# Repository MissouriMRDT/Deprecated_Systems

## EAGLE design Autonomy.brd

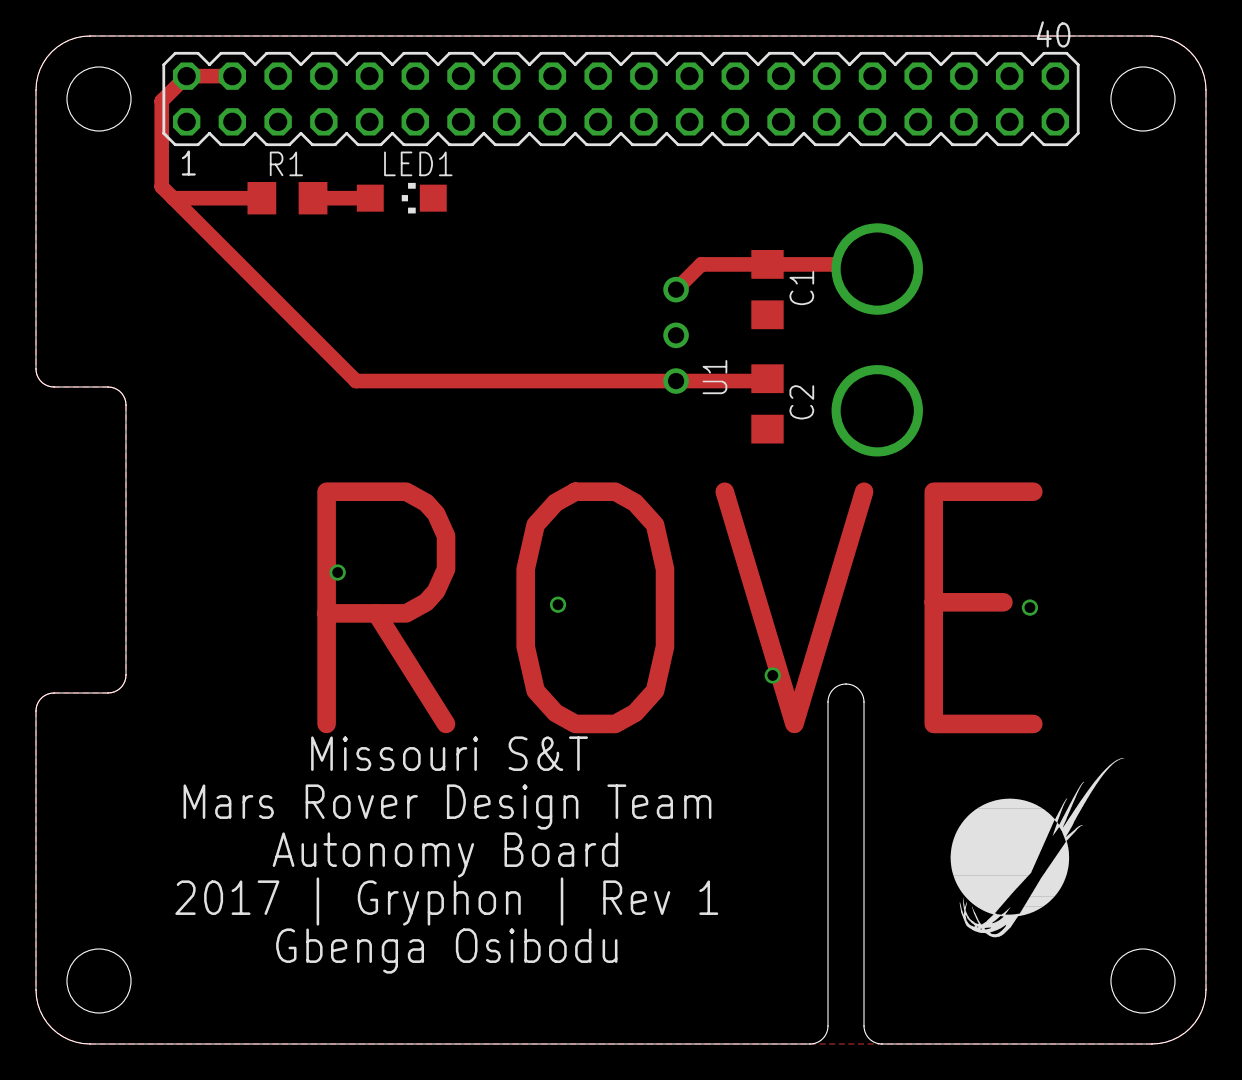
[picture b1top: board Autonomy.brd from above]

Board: 2 copper layers, 65.0 x 56.0 mm, 12 parts (0 on the bottom side), 4 nets.

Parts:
C1, C2: 10uF; C1206
J1: APP_2POS_CONFIG12V_HORIZ; APP45_12V_HORIZ_CONFIG
K1: MA20-2
LED1: CHIPLED_1206
R1: 330; R1206
U1: OKI-78SR-5/1.5-W36HC; OKI-78SR_HORIZ
U$1, U$2, U$3, U$4: #6_SCREW
U$5: MRDT_LOGO

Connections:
+5V: C2.1, K1.2, K1.4, R1.1, U1.3
+12V: C1.1, J1.12V, U1.1
GND: C1.2, C2.2, J1.GND, K1.6, K1.9, K1.14, K1.20, K1.25, K1.30, K1.34, K1.39, LED1.C, U1.2
unnamed: LED1.A, R1.2

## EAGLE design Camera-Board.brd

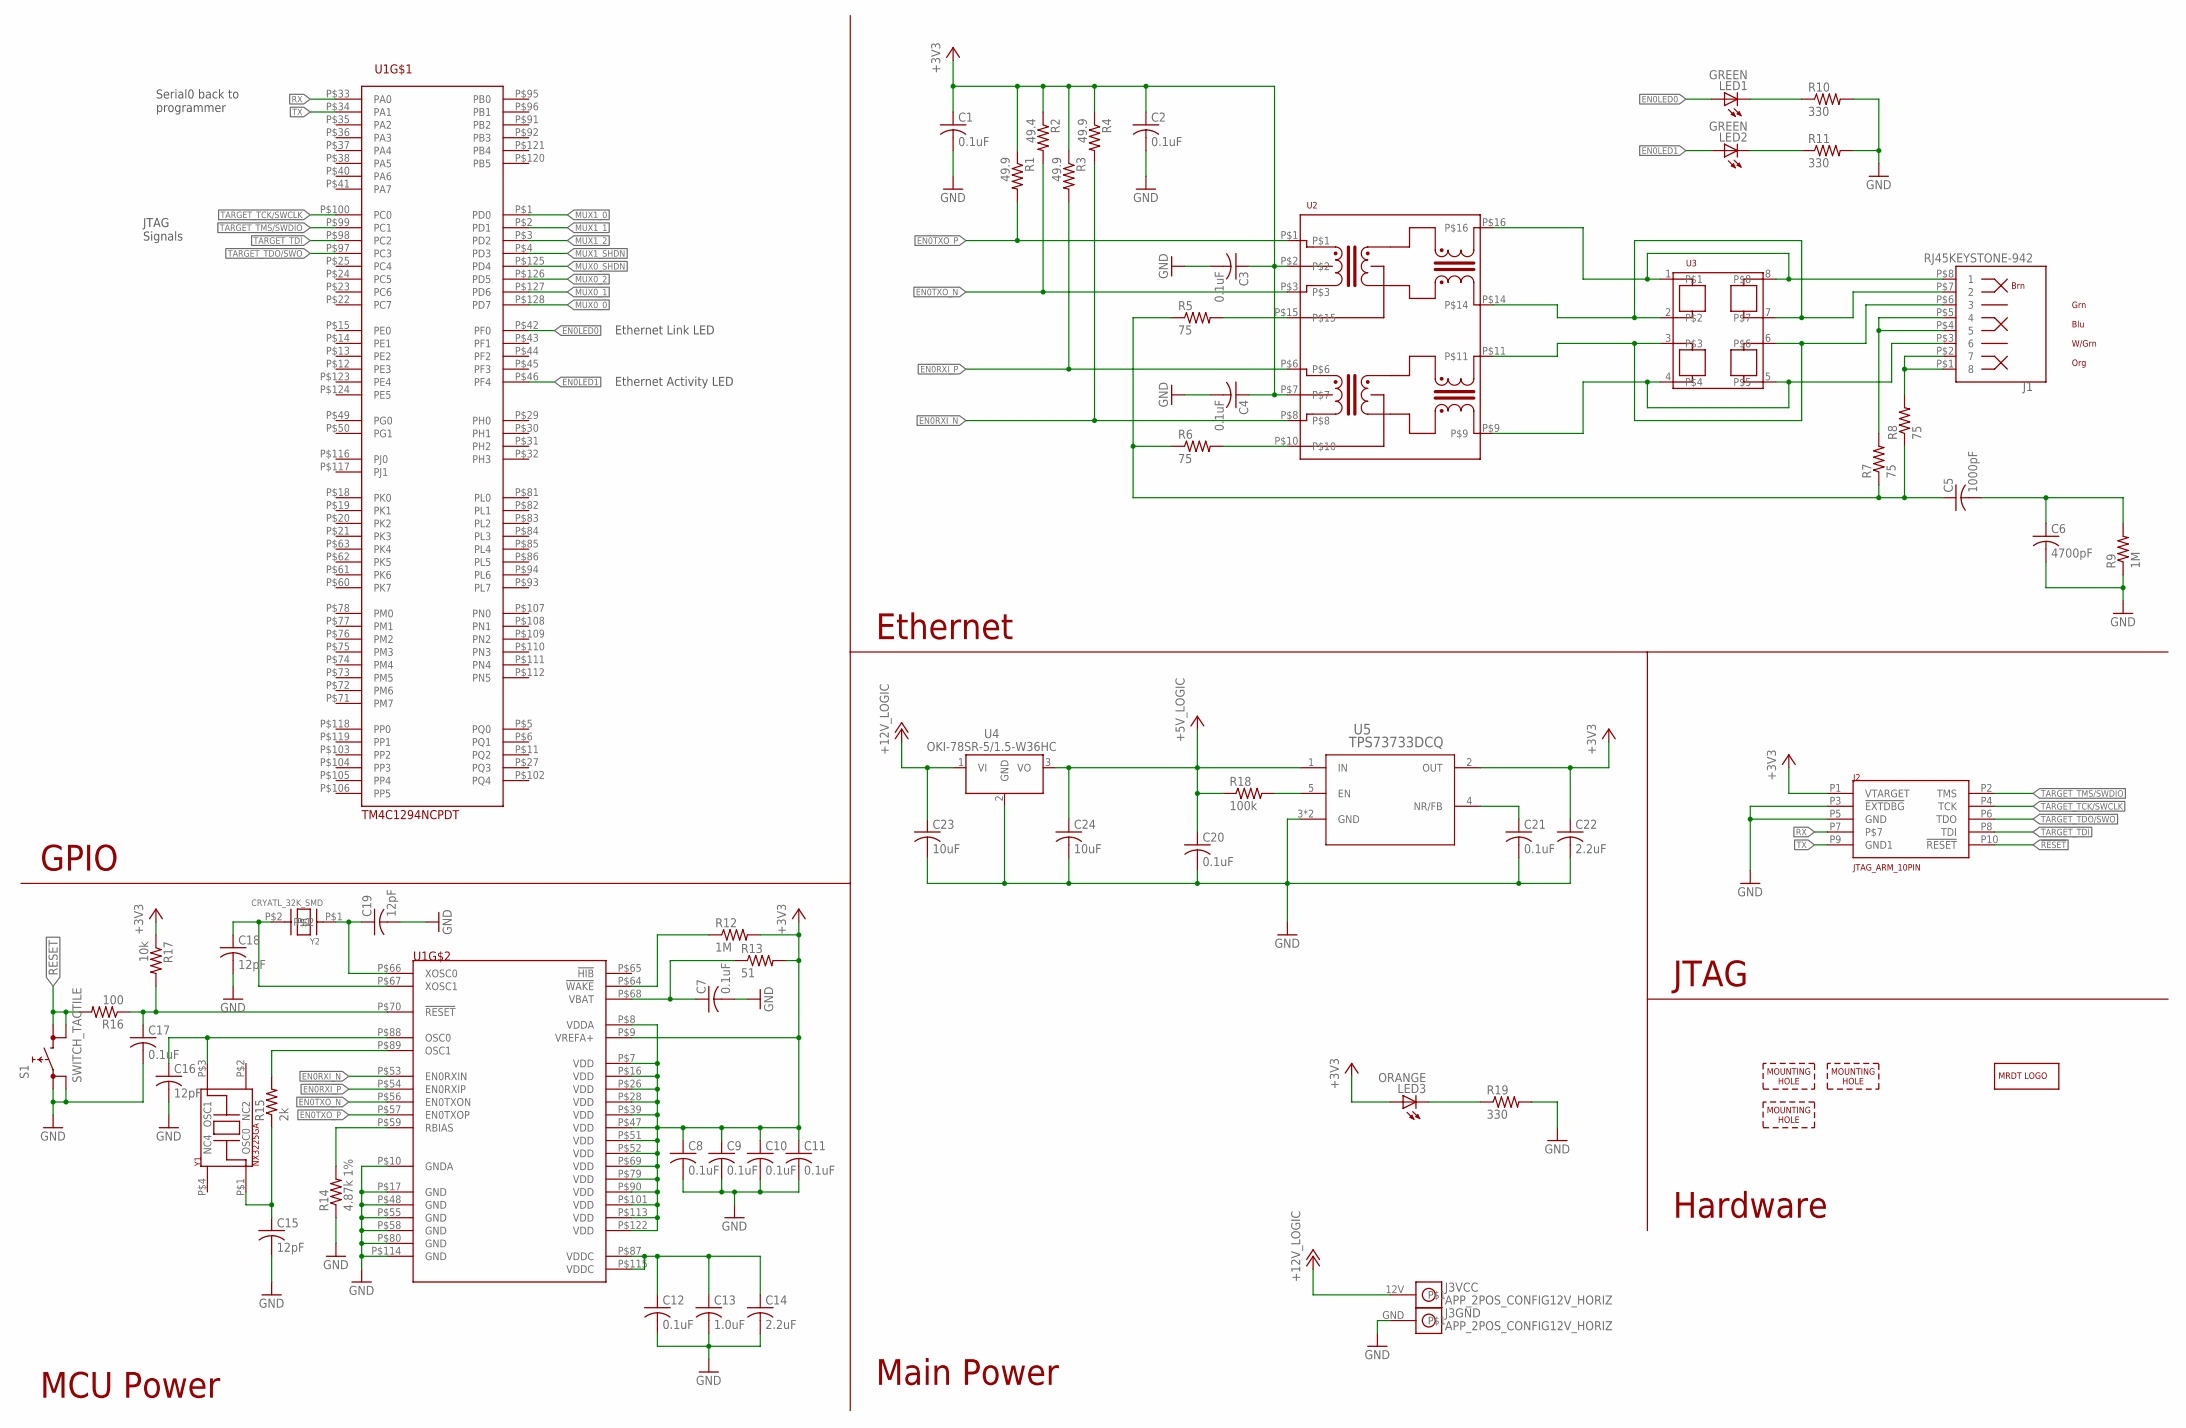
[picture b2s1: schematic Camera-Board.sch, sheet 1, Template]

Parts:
C1, C2, C3, C4, C7, C8, C9, C10, C11, C12, C17, C20, C21: 0.1uF; C0603
C5: 1000pF; C0603
C6: 4700pF; C1206
C13: 1.0uF; C0603
C14, C22: 2.2uF; C0603
C15, C16, C18, C19: 12pF; C0603
C23, C24: 10uF; C1206
J1: RJ45KEYSTONE-942; KEYSTONE-942
J2: JTAG_ARM_10PIN; CON_2X5_50MIL
J3: APP_2POS_CONFIG12V_HORIZ; APP45_12V_HORIZ_CONFIG
LED1, LED2: GREEN; CHIP-LED0603
LED3: ORANGE; CHIP-LED0603
R1, R3, R4: 49.9; R0603
R2: 49.4; R0603
R5, R6, R7, R8: 75; R0603
R9: 1M; R1206
R10, R11, R19: 330; R0603
R12: 1M; R0603
R13: 51; R0603
R14: 4.87k 1%; R0603
R15: 2k; R0603
R16: 100; R0603
R17: 10k; R0603
R18: 100k; R0603
S1: SWITCH_TACTILE; SWITCH_6MM_6MM_TE_CON_SMD
U1: TM4C1294NCPDT; TQFP-128
U2: HX1198FNL
U3: SLVU2.8-4; SOIC8
U4: OKI-78SR-5/1.5-W36HC; OKI-78SR_HORIZ
U5: TPS73733DCQ; SOT-223-6
U$1: MRDT_LOGO
U$2, U$3, U$4: MOUNTING_HOLE#6; #6_SCREW
Y1: NX3225GA; NDK3.2X2.5
Y2: CRYATL_32K_SMD; CRYSTAL_32K_SMD

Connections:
!RESET: J2.P10 (!RESET), R16.2, S1.P$3 (1), S1.P$4 (1)
+3V3: C1.1, C2.1, C3.1, C4.1, C8.1, C9.1, C10.1, C11.1, C22.1, J2.P1 (VTARGET), LED3.A, R1.1, R2.1, R3.1, R4.1, R12.2, R13.2, R17.1, U1.P$7 (VDD), U1.P$8 (VDDA), U1.P$9 (VREFA+), U1.P$16 (VDD), U1.P$26 (VDD), U1.P$28 (VDD), U1.P$39 (VDD), U1.P$47 (VDD), U1.P$51 (VDD), U1.P$52 (VDD), U1.P$69 (VDD), U1.P$79 (VDD), U1.P$90 (VDD), U1.P$101 (VDD), U1.P$113 (VDD), U1.P$122 (VDD), U2.P$2, U2.P$7, U5.2 (OUT)
+5V_LOGIC: C20.1, C24.1, R18.1, U4.3 (VO), U5.1 (IN); also elsewhere on the board
+12V_LOGIC: C23.1, J3.12V, U4.1 (VI)
EN0LED0: LED1.A, U1.P$42 (PF0)
EN0LED1: LED2.A, U1.P$46 (PF4)
EN0RXI_N: R4.2, U1.P$53 (EN0RXIN), U2.P$8
EN0RXI_P: R3.2, U1.P$54 (EN0RXIP), U2.P$6
EN0TXO_N: R2.2, U1.P$56 (EN0TXON), U2.P$3
EN0TXO_P: R1.2, U1.P$57 (EN0TXOP), U2.P$1
GND: C1.2, C2.2, C3.2, C4.2, C6.2, C7.2, C8.2, C9.2, C10.2, C11.2, C12.2, C13.2, C14.2, C15.2, C16.2, C17.2, C18.2, C19.2, C20.2, C21.2, C22.2, C23.2, C24.2, J2.P3 (!EXTDBG), J2.P5 (GND), J3.GND, R9.1, R10.2, R11.2, R14.1, R19.2, S1.P$1 (0), S1.P$2 (0), U1.P$10 (GNDA), U1.P$17 (GND), U1.P$48 (GND), U1.P$55 (GND), U1.P$58 (GND), U1.P$80 (GND), U1.P$114 (GND), U4.2 (GND), U5.3 (GND), U5.6 (GND); also elsewhere on the board
MUX0_0: U1.P$1 (PD0); also elsewhere on the board
MUX0_1: U1.P$2 (PD1); also elsewhere on the board
MUX0_2: U1.P$3 (PD2); also elsewhere on the board
MUX0_SHDN: U1.P$4 (PD3); also elsewhere on the board
MUX1_0: U1.P$128 (PD7); also elsewhere on the board
MUX1_1: U1.P$127 (PD6); also elsewhere on the board
MUX1_2: U1.P$126 (PD5); also elsewhere on the board
MUX1_SHDN: U1.P$125 (PD4); also elsewhere on the board
N_$1: R5.2, U2.P$15
N_$3: R6.2, U2.P$10
N_$4: J1.P$7 (2), U2.P$14, U3.2, U3.7
N_$5: J1.P$6 (3), U2.P$11, U3.3, U3.6
N_$6: J1.P$8 (1), U2.P$16, U3.1, U3.8
N_$7: J1.P$3 (6), U2.P$9, U3.4, U3.5
N_$8: LED2.C, R11.1
N_$9: LED1.C, R10.1
N_$10: C7.1, R13.1, U1.P$68 (VBAT)
N_$11: J1.P$4 (5), J1.P$5 (4), R7.2
N_$12: R12.1, U1.P$64 (!WAKE)
N_$13: J1.P$1 (8), J1.P$2 (7), R8.2
N_$14: C5.1, R5.1, R6.1, R7.1, R8.1
N_$15: C5.2, C6.1, R9.2
N_$16: C12.1, C13.1, C14.1, U1.P$87 (VDDC), U1.P$115 (VDDC)
N_$17: R15.2, U1.P$89 (OSC1)
N_$18: C16.1, U1.P$88 (OSC0), Y1.P$3 (OSC1)
N_$19: R14.2, U1.P$59 (RBIAS)
N_$20: C17.1, R16.1, R17.2, U1.P$70 (!RESET)
N_$21: C15.1, R15.1, Y1.P$1 (OSC0)
N_$22: C18.1, U1.P$67 (XOSC1), Y2.P$2
N_$23: C19.1, U1.P$66 (XOSC0), Y2.P$1
N_$25: R18.2, U5.5 (EN)
N_$26: LED3.C, R19.1
N_$27: C21.1, U5.4 (NR/FB)
RX: J2.P7, U1.P$33 (PA0)
TARGET_TCK/SWCLK: J2.P4 (TCK), U1.P$100 (PC0)
TARGET_TDI: J2.P8 (TDI), U1.P$98 (PC2)
TARGET_TDO/SWO: J2.P6 (TDO), U1.P$97 (PC3)
TARGET_TMS/SWDIO: J2.P2 (TMS), U1.P$99 (PC1)
TX: J2.P9 (GND1), U1.P$34 (PA1)

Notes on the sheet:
Ethernet
GPIO
MCU Power
Main Power
JTAG
Hardware
Serial0 back to programmer
JTAG Signals
Ethernet Link LED
Ethernet Activity LED

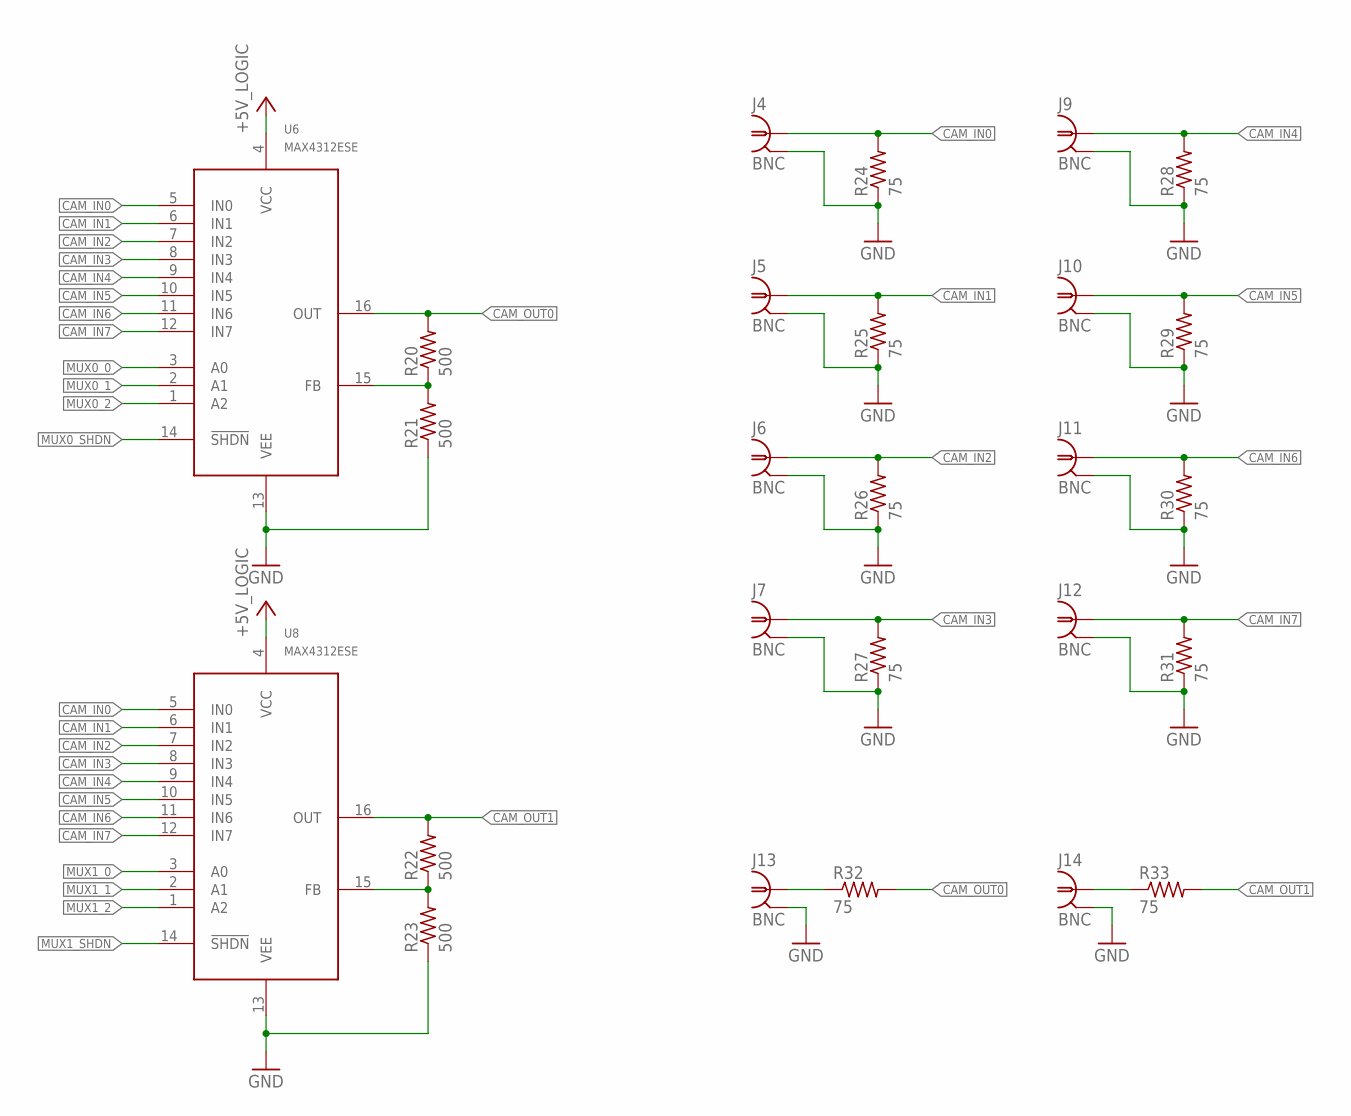
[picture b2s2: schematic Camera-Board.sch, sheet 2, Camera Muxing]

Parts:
J4, J5, J6, J7, J9, J10, J11, J12, J13, J14: BNC; MOLEX-0731711640-BNC
R20, R21, R22, R23: 500; R0603
R24, R25, R26, R27, R28, R29, R30, R31, R32, R33: 75; R0603
U6, U8: MAX4312ESE; SOIC16

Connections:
+5V_LOGIC: U6.4 (VCC), U8.4 (VCC); also elsewhere on the board
CAM_IN0: J4.P$1 (1), R24.2, U6.5 (IN0), U8.5 (IN0)
CAM_IN1: J5.P$1 (1), R25.2, U6.6 (IN1), U8.6 (IN1)
CAM_IN2: J6.P$1 (1), R26.2, U6.7 (IN2), U8.7 (IN2)
CAM_IN3: J7.P$1 (1), R27.2, U6.8 (IN3), U8.8 (IN3)
CAM_IN4: J9.P$1 (1), R28.2, U6.9 (IN4), U8.9 (IN4)
CAM_IN5: J10.P$1 (1), R29.2, U6.10 (IN5), U8.10 (IN5)
CAM_IN6: J11.P$1 (1), R30.2, U6.11 (IN6), U8.11 (IN6)
CAM_IN7: J12.P$1 (1), R31.2, U6.12 (IN7), U8.12 (IN7)
CAM_OUT0: R22.2, R33.2, U8.16 (OUT)
CAM_OUT1: R20.2, R32.2, U6.16 (OUT)
GND: J4.P$2 (2), J4.P$3 (2), J4.P$4 (2), J4.P$5 (2), J5.P$2 (2), J5.P$3 (2), J5.P$4 (2), J5.P$5 (2), J6.P$2 (2), J6.P$3 (2), J6.P$4 (2), J6.P$5 (2), J7.P$2 (2), J7.P$3 (2), J7.P$4 (2), J7.P$5 (2), J9.P$2 (2), J9.P$3 (2), J9.P$4 (2), J9.P$5 (2), J10.P$2 (2), J10.P$3 (2), J10.P$4 (2), J10.P$5 (2), J11.P$2 (2), J11.P$3 (2), J11.P$4 (2), J11.P$5 (2), J12.P$2 (2), J12.P$3 (2), J12.P$4 (2), J12.P$5 (2), J13.P$2 (2), J13.P$3 (2), J13.P$4 (2), J13.P$5 (2), J14.P$2 (2), J14.P$3 (2), J14.P$4 (2), J14.P$5 (2), R21.1, R23.1, R24.1, R25.1, R26.1, R27.1, R28.1, R29.1, R30.1, R31.1, U6.13 (VEE), U8.13 (VEE); also elsewhere on the board
MUX0_0: U8.3 (A0); also elsewhere on the board
MUX0_1: U8.2 (A1); also elsewhere on the board
MUX0_2: U8.1 (A2); also elsewhere on the board
MUX0_SHDN: U8.14 (!SHDN); also elsewhere on the board
MUX1_0: U6.3 (A0); also elsewhere on the board
MUX1_1: U6.2 (A1); also elsewhere on the board
MUX1_2: U6.1 (A2); also elsewhere on the board
MUX1_SHDN: U6.14 (!SHDN); also elsewhere on the board
unnamed: R20.1, R21.2, U6.15 (FB)
unnamed: R22.1, R23.2, U8.15 (FB)
unnamed: J14.P$1 (1), R33.1
unnamed: J13.P$1 (1), R32.1

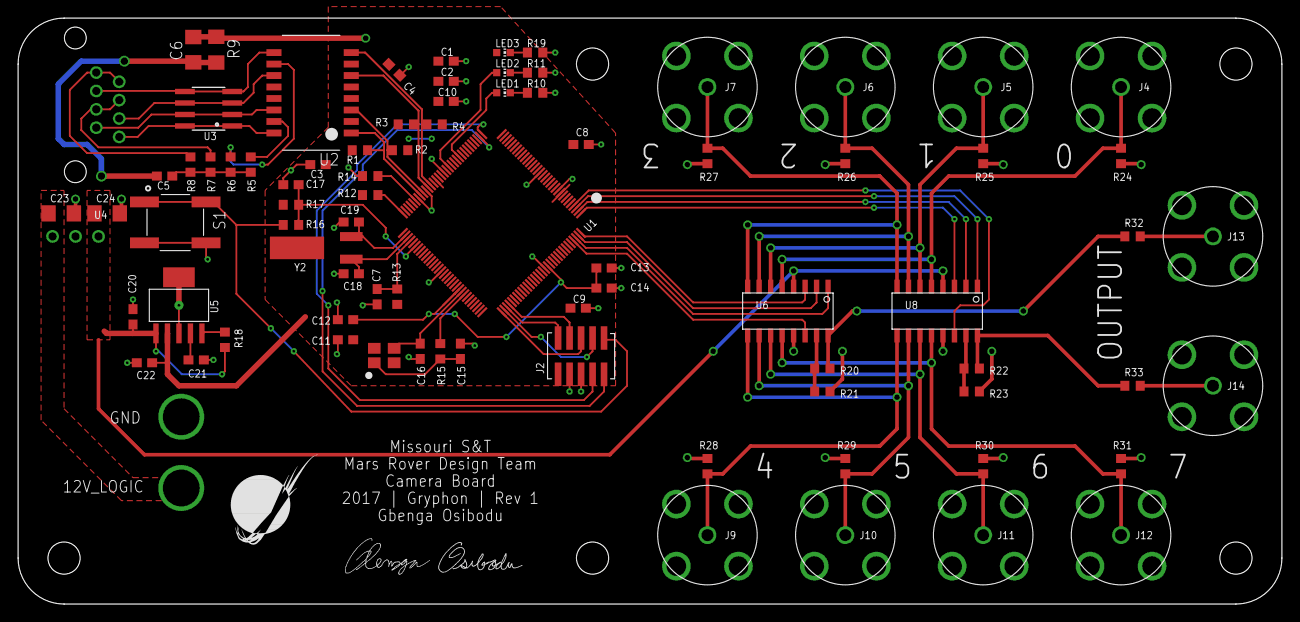
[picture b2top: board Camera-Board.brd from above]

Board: 2 copper layers, 139.7 x 64.8 mm, 90 parts (0 on the bottom side), 64 nets.

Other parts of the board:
U$6, U$7: MOUNTING_HOLE#6; #6_SCREW
U$8: SIG3

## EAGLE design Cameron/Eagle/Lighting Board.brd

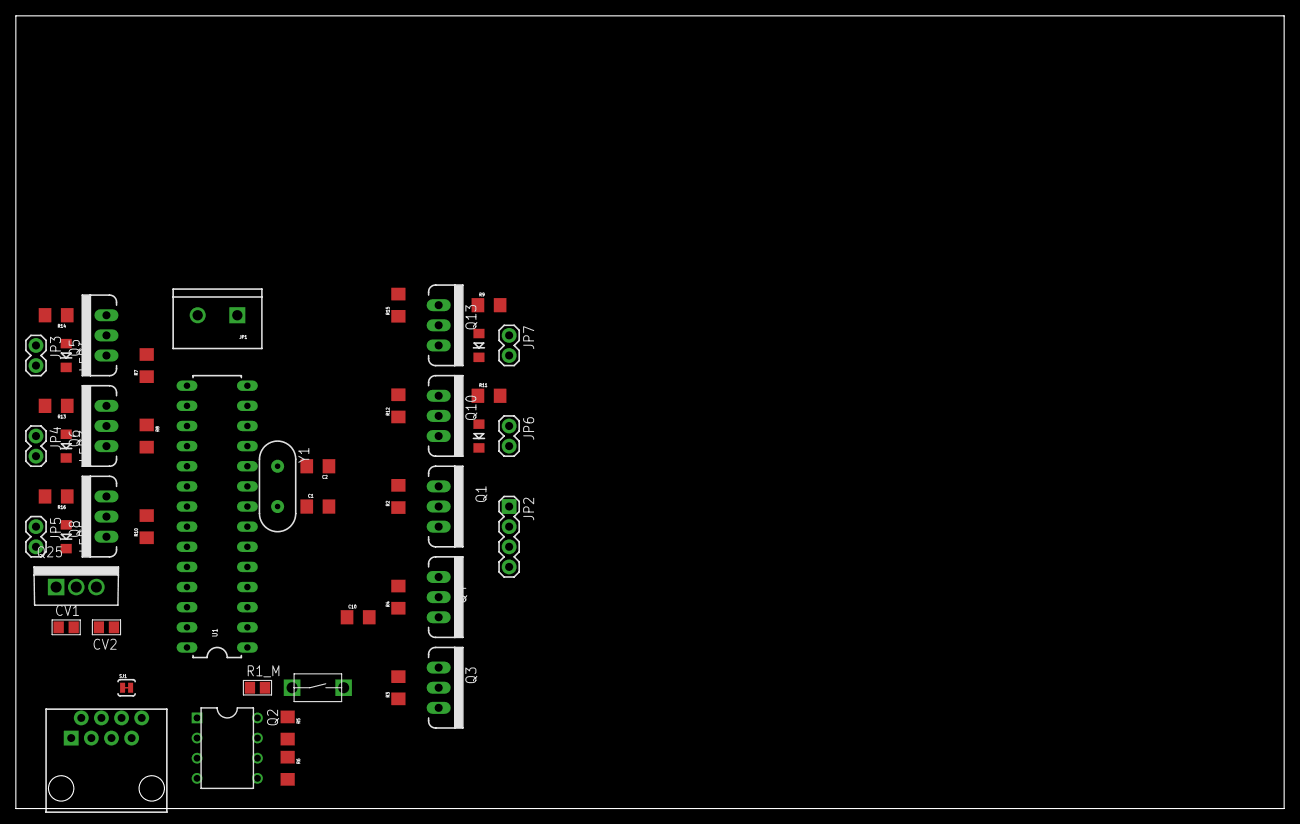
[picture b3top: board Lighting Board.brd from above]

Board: 2 copper layers, 160.0 x 100.0 mm, 48 parts (0 on the bottom side), 34 nets, no tracks yet.

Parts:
C1, C2: 0.1uF; 1206
C10: .1uF; 1206
CV1, CV2: C_0805
JP1: M025MM; SCREWTERMINAL-5MM-2
JP2: 1X04
JP3, JP4, JP5, JP6, JP7: M02PTH; 1X02
LED1, LED2, LED3, LED4, LED5: LED-1206
MS: J_MC32857; J_TOGGLE
Q1, Q3, Q4, Q5, Q6, Q8, Q10, Q13: MOSFET-NCHANNELFQP30N06L; TO220V
Q2: Q_LTC490; DIP8
Q25: LDO; TO-220
R1_M: 200; R_0805
R2, R3, R4, R7, R8, R10, R12, R15: 1k; 1206
R5, R6: 120 Ohm; 1206
R9, R11: 1206
R13, R14, R16: 200; 1206
SJ1: SOLDERJUMPERTRACE; SJ_2S-TRACE
U1: ATMEGA328P_PDIP; DIL28-3
U$1: RJ45-8PTH; RJ45-8
Y1: HC49US

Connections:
D1: Q10.1, R12.2, U1.13
D2: Q13.1, R15.2, U1.14
GND: C1.2, C2.2, C10.2, CV1.2, CV2.2, JP1.2, MS.P$1, Q1.3, Q2.4, Q3.3, Q4.3, Q5.3, Q6.3, Q8.3, Q10.3, Q13.3, Q25.2, R2.1, R3.1, R4.1, R7.1, R8.1, R10.1, R12.1, R15.1, SJ1.1, U1.8, U1.22
unnamed: Q2.5, R6.2, U$1.1
unnamed: C2.1, U1.10, Y1.1
unnamed: LED1.A, R9.1
unnamed: LED2.A, R11.1
unnamed: LED3.A, R13.1
unnamed: LED4.A, R14.1
unnamed: LED5.A, R16.1
unnamed: Q2.6, R6.1, U$1.2
unnamed: Q2.7, R5.2, U$1.6
unnamed: Q2.8, R5.1, U$1.3
unnamed: SJ1.2, U$1.7, U$1.8
unnamed: C1.1, U1.9, Y1.2
unnamed: JP2.2, Q1.2
unnamed: JP2.3, Q3.2
unnamed: JP2.4, Q4.2
unnamed: MS.P$2, R1_M.1, U1.1
N%2: JP4.2, LED3.C, Q6.2
N%3: JP3.2, LED4.C, Q5.2
N%106: JP5.2, LED5.C, Q8.2
N%107: JP6.2, LED2.C, Q10.2
N%110: JP7.2, LED1.C, Q13.2
PWM1: Q3.1, R3.2, U1.5
PWM2: Q4.1, R4.2, U1.11
PWM3: Q1.1, R2.2, U1.12
PWM4: Q5.1, R7.2, U1.15
PWM5: Q6.1, R8.2, U1.16
PWM6: Q8.1, R10.2, U1.17
RXD: Q2.2, U1.2
TXD: Q2.3, U1.3
V5: C10.1, CV2.1, Q2.1, Q25.3, R1_M.2, U1.7, U1.20
VIN: CV1.1, JP1.1, JP2.1, JP3.1, JP4.1, JP5.1, JP6.1, JP7.1, Q25.1, R9.2, R11.2, R13.2, R14.2, R16.2

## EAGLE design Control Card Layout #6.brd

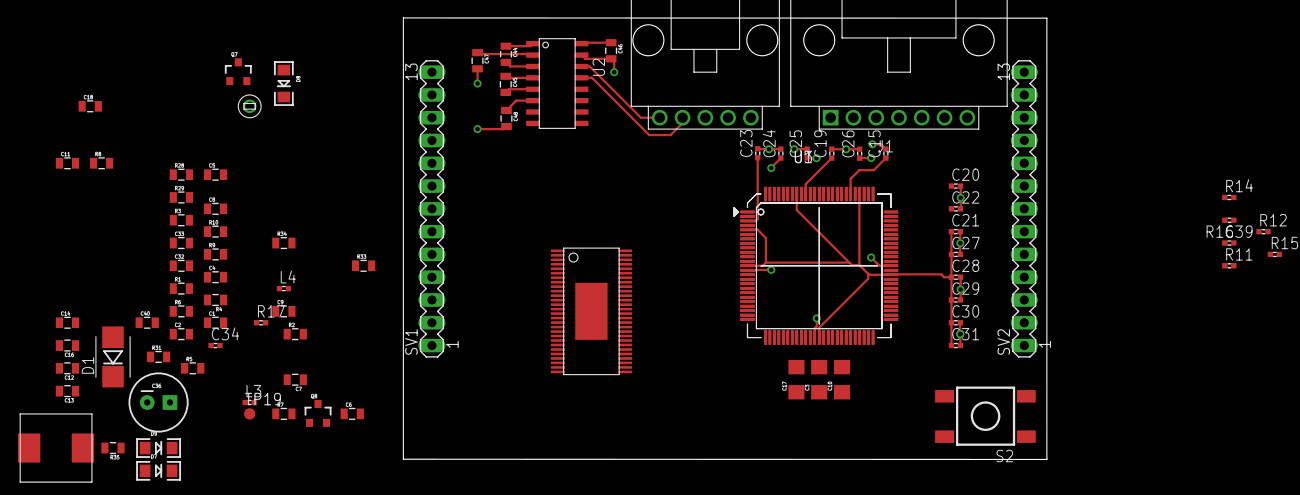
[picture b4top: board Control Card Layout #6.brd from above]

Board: 4 copper layers, 71.7 x 49.2 mm, 84 parts (0 on the bottom side), 85 nets.

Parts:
C1: 6800p; 0805
C2: 120p; 0805
C3: 2.2u; 1206
C4: .022u; 0805
C5, C8, C32: 1u; 0805
C6, C7: 2200p; 0805
C9, C11, C12, C13, C14, C18, C33, C44, C45, C46, C47, C48: 0.1u; 0805
C10, C17: 4.7u; 1206
C15, C19, C20, C21, C22, C23, C24, C25, C26, C27, C28, C29, C30, C31: 2.2u; C0402
C16: 0.015u; 0805
C34, C39: 0.1u; C0402
C36: 47u; CPOL-RADIAL-100UF-25V
C40: .015u; 0805
D1: DIODE-ZENERSMB; SMB-DIODE
D7, D8, D9: LED-1206
J1: SL07-HORIZ; MOLEX-70551-0006
L3: BKP1005HS221-T; R0402
L4: BLM15PD600SN1D; R0402
Q7, Q8: MOSFET-PCHANNEL; SOT23-3
R1: 205k; 0805
R2: 16.2k; 0805
R3: 31.6k; 0805
R4, R5, R6, R7: 10k; 0805
R8: 150k; 0805
R9, R10: 56; 0805
R11, R12, R14, R17: 2.2k; R0402
R15, R16: 820; R0402
R28, R29: 1k; 0805
R31: 100; 0805
R33, R34, R35: 330; 0805
S2: TP-1138K9-BE1125; FSMJSMA
SV1, SV2: MA13-1
TP19: TESTPAD_TPB1,27; TESTPAD_B1,27
U1, U3: TMS320F28069MPZT; PQFP100
U2: MAX3232D; SOIC16
U$1: DRV8301; DCA
U$4: 5PIN
U$10: TEST_POINT_0.1INDIAM
U$14: 33u; INDUCTOR_DR74

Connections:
232_RX: U2.13, U$4.4
232_TX: U2.14, U$4.5
+3V3: C22.1, C34.1, L3.2, L4.2, R11.2, R15.2, R16.2, U1.46
ASENSE: SV1.10, U1.29
BSENSE: SV1.8, U1.21
CSENSE: SV1.6, U1.30
DC_CAL: R29.1, U3.48, U$1.12
EN_GATE: R28.1, U3.42, U$1.16
GH_A: SV1.1, U$1.47
GH_B: SV1.2, U$1.42
GH_C: SV1.3, U$1.37
GL_A: SV1.9, U$1.45
GL_B: SV1.11, U$1.40
GL_C: SV1.13, U$1.35
GND: C1.2, C2.1, C3.2, C5.2, C6.2, C7.2, C8.2, C9.2, C10.2, C15.2, C16.2, C17.2, C18.1, C19.2, C20.2, C21.2, C22.2, C23.2, C24.2, C25.2, C26.2, C27.2, C28.2, C29.2, C30.2, C31.2, C32.1, C33.1, C34.2, C36.2, C39.2, C40.2, C46.2, C47.2, C48.2, D1.A, J1.7, R1.1, R4.1, R8.2, R12.1, R14.1, R17.1, R28.2, R29.2, R33.2, R34.2, R35.2, S2.P$1, S2.P$2, U1.4, U1.15, U1.26, U1.27, U1.36, U1.47, U1.62, U1.80, U1.90, U1.92, U2.15, U$1.28, U$1.34, U$1.P$2, U$4.3
GPIO34: R12.2, R15.1, U3.68
INH_A: U3.87, U$1.17
INH_B: U3.84, U$1.19
INH_C: U3.9, U$1.21
INL_A: U3.86, U$1.18
INL_B: U3.83, U$1.20
INL_C: U3.10, U$1.22
unnamed: C2.2, R2.1, U$1.2
unnamed: C1.1, R2.2
unnamed: R3.1, R4.2, U$1.3
unnamed: R1.2, U$1.1
unnamed: R8.1, U$1.7
unnamed: C4.1, U$1.14
unnamed: C4.2, U$1.15
unnamed: C3.1, U$1.13
unnamed: C5.1, U$1.23
unnamed: R9.1, U$1.25
unnamed: R10.1, U$1.26
unnamed: C8.1, U$1.27
unnamed: C23.1, U1.3
unnamed: C24.1, U1.14
unnamed: C25.1, U1.37
unnamed: C26.1, U1.63
unnamed: C15.1, U1.81
unnamed: C11.1, U$1.38
unnamed: D7.C, R33.1
unnamed: C12.1, U$1.43
unnamed: D8.C, R34.1
unnamed: D9.C, R35.1
unnamed: D9.A, Q8.3
unnamed: C13.1, U$1.48
unnamed: C14.1, U$1.52
unnamed: C14.2, D1.C, U$1.50, U$1.51, U$14.P$1
unnamed: D8.A, Q7.3
unnamed: R31.2, U$4.1
unnamed: C16.1, U$1.56
unnamed: C19.1, U1.91
unnamed: C44.1, U2.1
unnamed: C44.2, U2.3
unnamed: C45.1, U2.4
unnamed: C45.2, U2.5
unnamed: C48.1, U2.6
unnamed: C47.1, U2.2
NFAULT: Q7.1, R7.1, U3.100, U$1.6
NOCTW: Q8.1, R6.1, U3.99, U$1.5
NSCS: U1.64, U$1.8
PVDD: C9.1, C10.1, C17.1, C18.2, SV1.12, U$1.29, U$1.53, U$1.54
PWM_IN: C40.1, R31.1, U3.75
PWRGD: R5.1, U$1.4
RESET#: C39.1, R11.1, S2.P$3, S2.P$4, U1.11
SCLK: U1.51, U$1.11
SDI: U3.55, U$1.9
SDO: U3.52, U$1.10
SH_A: C13.2, SV1.4, U$1.46
SH_B: C12.2, SV1.5, U$1.41
SH_C: C11.2, SV1.7, U$1.36
SL_A: SV2.1, U$1.33, U$1.44
SL_B: SV2.2, U$1.31, U$1.39
SO1: C6.1, R9.2, U1.23
SO2: C7.1, R10.2, U1.28
SP1: SV2.3, U$1.32
SP2: SV2.4, U$1.30
TCK: J1.1, U1.67
TDI: J1.2, U1.71
TDO: J1.3, R14.2, R16.1, U1.70
TMS: J1.4, U1.72
TRST: J1.5, R17.2, U1.12
VCC: C32.2, C33.2, C36.1, C46.1, D7.A, J1.6, Q7.2, Q8.2, R3.2, R5.2, R6.2, R7.2, U2.16, U$1.24, U$1.49, U$10.P$1, U$14.P$2
VDDA: C20.1, L3.1, TP19.TP, U1.25, U3.25
VDDIO: C21.1, C27.1, C28.1, C29.1, C30.1, C31.1, L4.1, U1.5, U1.13, U1.38, U1.61, U1.79, U1.93

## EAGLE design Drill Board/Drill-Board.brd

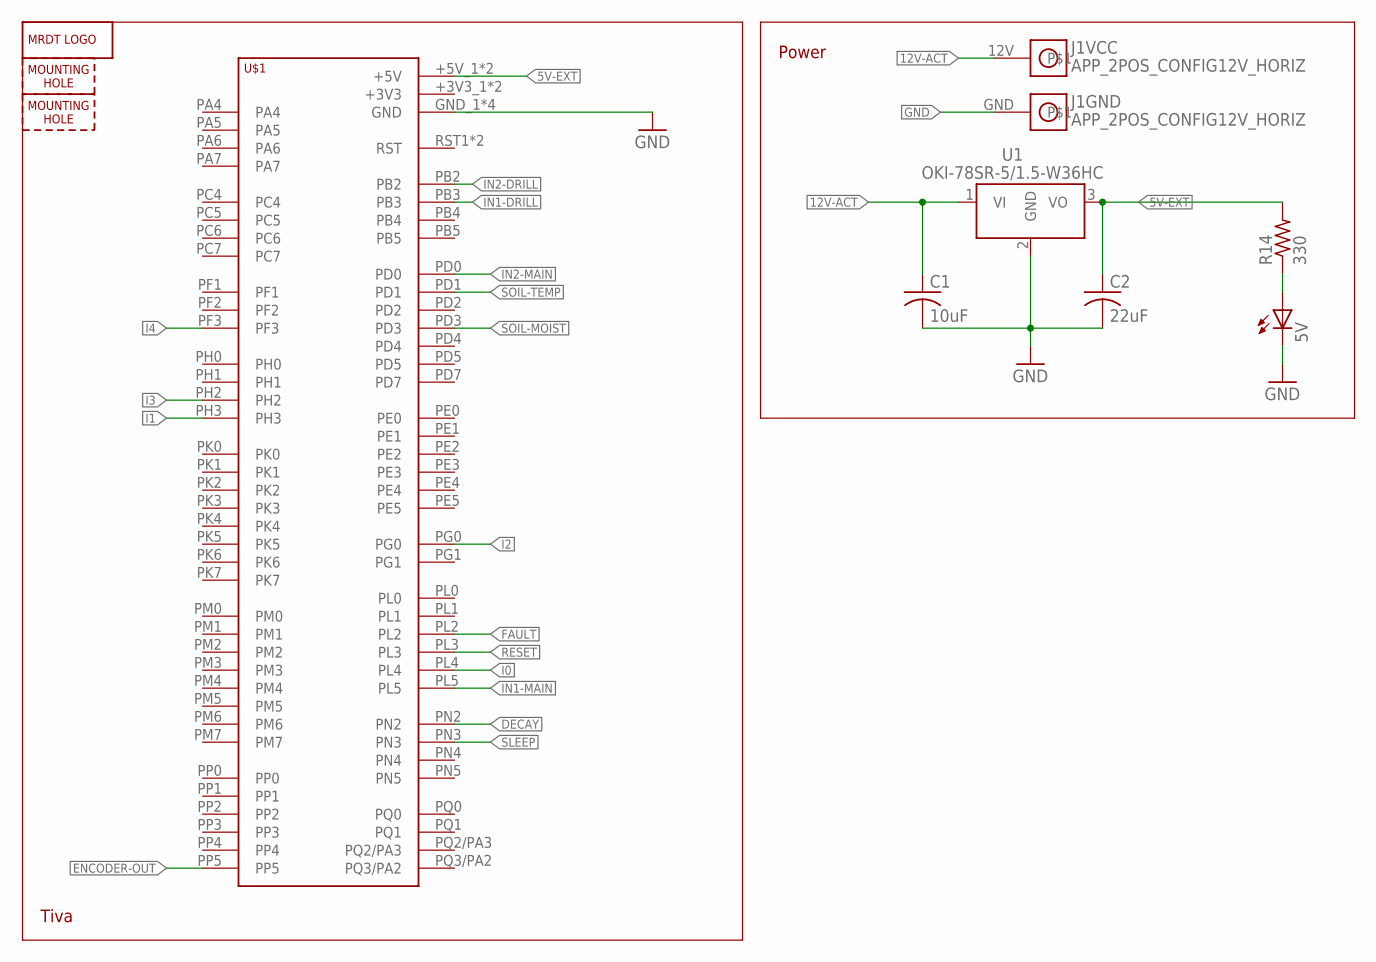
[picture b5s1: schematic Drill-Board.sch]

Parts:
5V: LEDCHIP-LED0805; CHIP-LED0805
C1: 10uF; C0805
C2: 22uF; C0805
H1, H5: MOUNTING_HOLE#6; #6_SCREW
J1: APP_2POS_CONFIG12V_HORIZ; APP45_12V_HORIZ_CONFIG
LOGO1: MRDT_LOGO
R14: 330; M0805
U1: OKI-78SR-5/1.5-W36HC; OKI-78SR_HORIZ
U$1: TIVA-1294; TIVA-C-CONNECTED

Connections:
5V-EXT: C2.1, R14.2, U1.3 (VO), U$1.+5V_1 (+5V), U$1.+5V_2 (+5V)
12V-ACT: C1.1, J1.12V, U1.1 (VI)
DECAY: U$1.PN2
ENCODER-OUT: U$1.PP5
FAULT: U$1.PL2
GND: 5V.C, C1.2, C2.2, J1.GND, U1.2 (GND), U$1.GND_1 (GND), U$1.GND_2 (GND), U$1.GND_3 (GND), U$1.GND_4 (GND)
I0: U$1.PL4
I1: U$1.PH3
I2: U$1.PG0
I3: U$1.PH2
I4: U$1.PF3
IN1-DRILL: U$1.PB3
IN1-MAIN: U$1.PL5
IN2-DRILL: U$1.PB2
IN2-MAIN: U$1.PD0
unnamed: 5V.A, R14.1
RESET: U$1.PL3
SLEEP: U$1.PN3
SOIL-MOIST: U$1.PD3
SOIL-TEMP: U$1.PD1

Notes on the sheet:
Power
Tiva

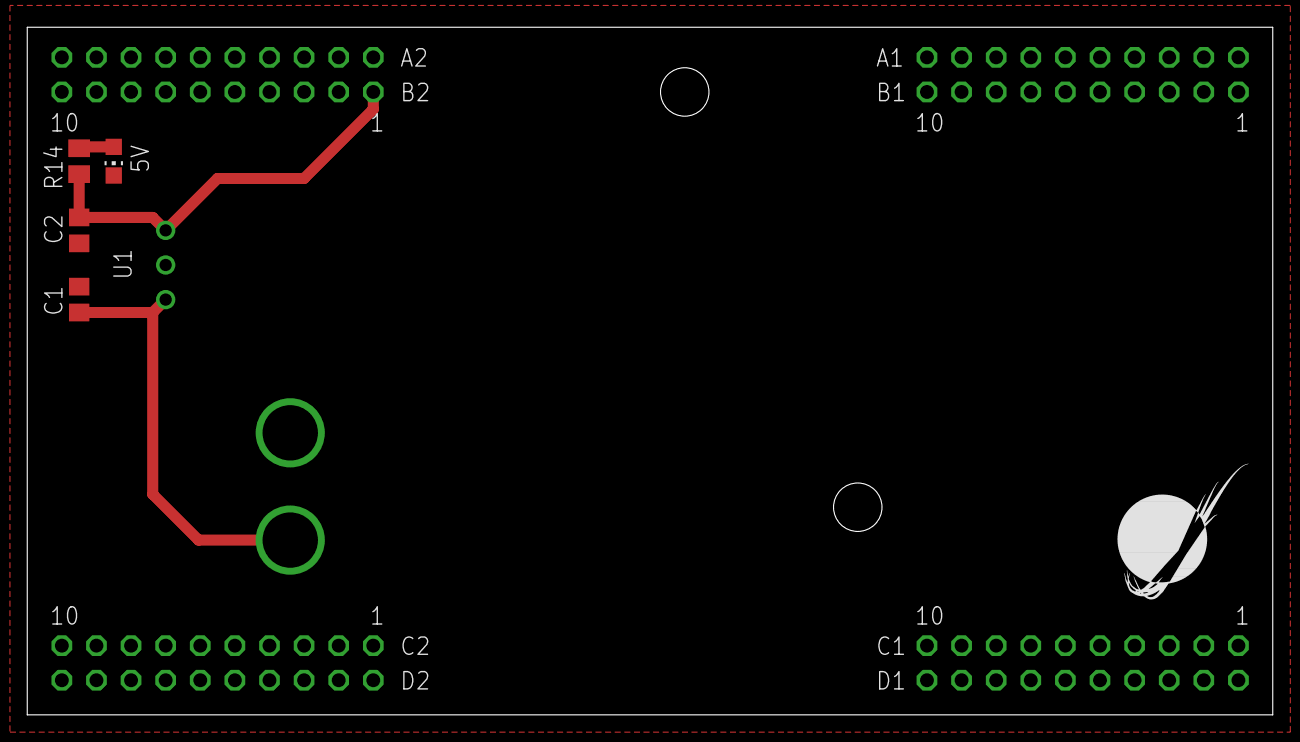
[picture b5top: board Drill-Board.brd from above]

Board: 2 copper layers, 91.4 x 50.5 mm, 10 parts (0 on the bottom side), 4 nets.

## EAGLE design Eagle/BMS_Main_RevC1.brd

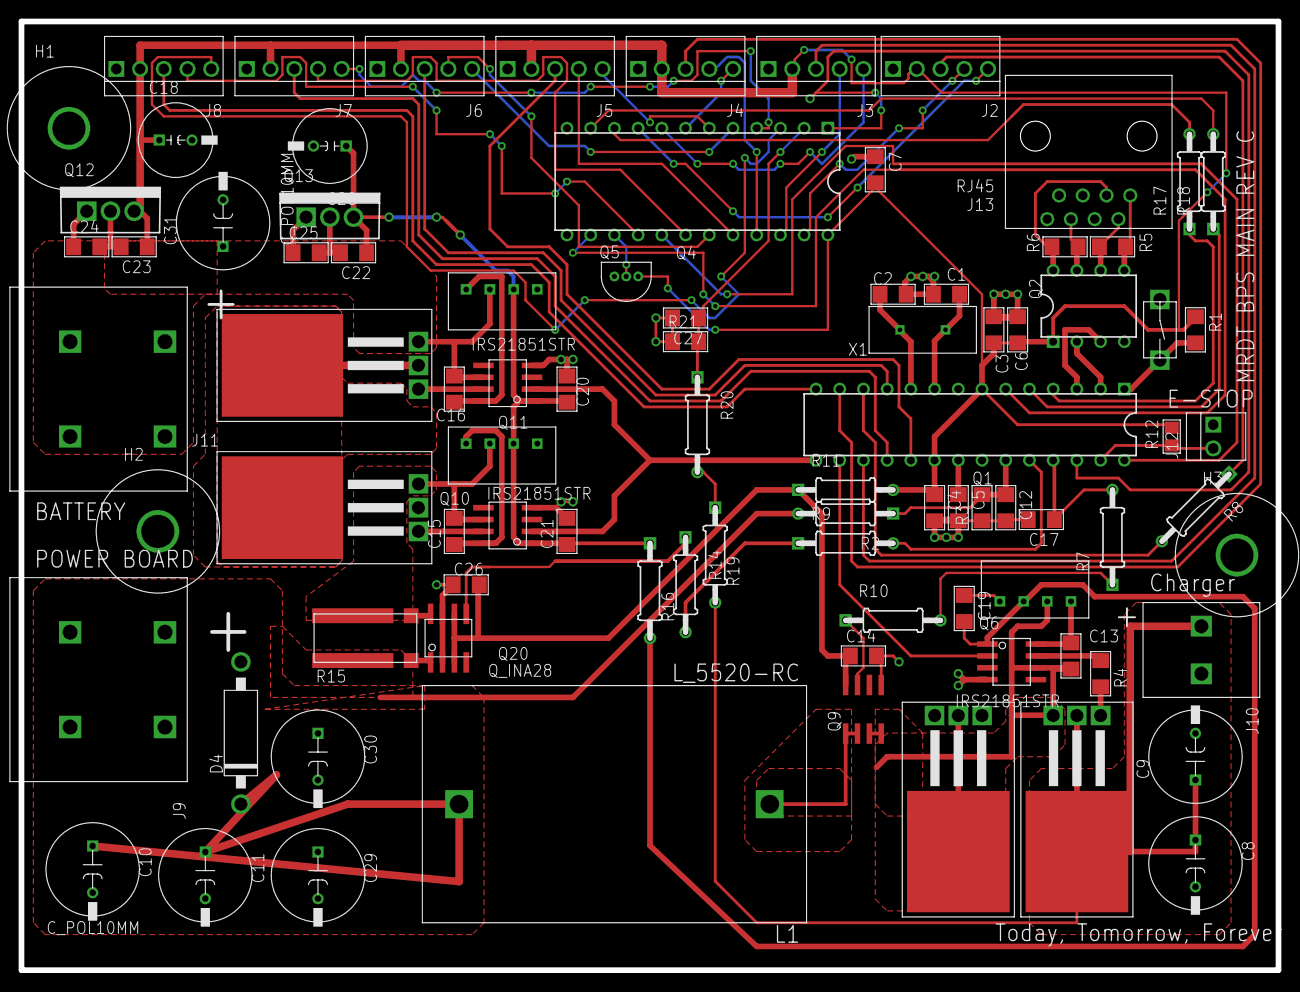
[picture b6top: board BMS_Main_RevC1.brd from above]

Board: 2 copper layers, 134.6 x 101.6 mm, 88 parts (0 on the bottom side), 73 nets.

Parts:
C1, C2, C3, C4, C5, C6, C7, C12, C13, C14, C15, C16, C17, C19, C20, C21, C22, C23, C24, C25, C26, C27: C_1206
C8, C9, C11, C29, C30: C_10MM
C10, C31: C_POL10MM; C_10MM
C18, C28: C_POL8MM; C_8MM
D1: MBR20H; TO-220-FLAT
D4: TVSDiode; DIODE_D3.5MM_LS15.24MM
H1, H2, H3: H_MNTHOLE_#6
J1: J_MC32857; J_TOGGLE
J2, J3, J4, J5, J6, J7, J8: J_MTA100_5P
J9, J11: J_0399700102; J_2CONHC
J10: THERM_BLOCK_2
J12: J_MTA100_2P
J13: RJ45; RJ45-CAT5E
L1: L_5520-RC
P1: IK1212SA; TME1215S
P2, P3: TME1215S
Q1: Q_ATMEGA328P; DIP28
Q2: Q_LTC490; DIP8
Q3: CSD18532; TO-220-FLAT
Q4: Q_CD4097B; WDIP24
Q5: Q_LM35TO-92; TO-92-3
Q6, Q10, Q11: IRS21851STR; SOIC8
Q7, Q8: Q_CSD18532KCSPCB; TO-220-FLAT
Q9: Q_SO8
Q12, Q13: Q_LDO; TO-220
Q20: Q_INA28; SOIC8
R1, R3, R4, R5, R6, R21: R_1206
R2, R7, R8, R9, R10, R11, R14, R16, R17, R18, R19, R20: R_1/4W
R12: R_0805
R15: R_FC4L
X1: HC49S; HC-49

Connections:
+5V: C3.2, C4.1, C6.1, C7.2, C18.+, C23.1, J2.2, J3.2, J4.2, J5.2, J6.2, J7.2, J8.2, Q1.7, Q1.20, Q2.1, Q4.24, Q5.1, Q12.3, R1.1, R11.2, R12.2
+5V1: C14.1, C26.1, Q9.8, Q20.3, Q20.6, R11.1
+12V: C20.1, C21.1, C22.1, C28.+, P2.2, P3.2, Q10.1, Q11.1, Q13.3, R16.1
+12V1: C19.2, P1.2, Q6.1, R16.2
A: Q1.4, R17.1
B: Q1.5, R18.1
BATHIGH: C15.2, P2.3, Q8.3, Q10.6, R15.2
BATTERIES: C16.2, C24.1, C25.1, C31.P$1, J11.PIN1-1, J11.PIN1-2, P3.3, Q7.3, Q11.6, Q12.1, Q13.1
C: Q1.6, Q4.14
CURRENT: R7.1, R10.2
GATE1: J2.3, R8.1
GATE2: J3.3, Q1.17
GATE3: J4.3, Q1.13
GATE4: J5.3, Q1.19
GATE5: J6.3, Q1.11
GATE6: J7.3, Q1.18
GATE7: J8.3, Q1.14
GATE_B: Q6.7, R4.1
GND: C1.1, C2.1, C3.1, C4.2, C5.2, C6.2, C7.1, C8.P$2, C9.P$2, C10.P$2, C11.P$2, C12.2, C14.2, C17.2, C18.-, C19.1, C20.2, C21.2, C22.2, C23.2, C24.2, C25.2, C26.2, C27.2, C28.-, C29.P$2, C30.P$2, C31.P$2, D1.1, D1.3, D4.A, J1.P$1, J2.1, J3.1, J4.1, J5.1, J6.1, J7.1, J8.1, J9.PIN2-1, J9.PIN2-2, J10.P$1, J11.PIN2-1, J11.PIN2-2, J12.1, J13.7, J13.8, P1.1, P2.1, P3.1, Q1.8, Q1.22, Q2.4, Q4.12, Q4.13, Q5.3, Q6.4, Q9.5, Q10.4, Q11.4, Q12.2, Q13.2, Q20.2, Q20.7, R3.1, R21.1
IN: C8.P$1, C9.P$1, J10.P$2, Q3.2, Q3.4, R19.2
INT_BAT: Q7.2, Q7.4, Q8.4
IP-: L1.1, Q9.1, Q9.2
MAIN: C10.P$1, C11.P$1, C29.P$1, C30.P$1, D4.C, J9.PIN1-1, J9.PIN1-2, L1.2, R2.2, R15.1
MAINCURRENT: Q1.24, R9.2
unnamed: C2.2, Q1.10, X1.P$1
unnamed: C1.2, Q1.9, X1.P$2
unnamed: Q20.5, R14.1
unnamed: Q4.10, R17.2
unnamed: C5.1, Q1.21
unnamed: Q4.11, R18.2
unnamed: J1.P$2, Q1.1, R1.2
unnamed: Q9.7, R10.1
unnamed: R19.1, R20.2
unnamed: Q20.8, R15.SENSE2
unnamed: Q20.1, R15.SENSE1
unnamed: R9.1, R14.2
unnamed: C17.1, Q1.25, R7.2
unnamed: Q1.12, R8.2
unnamed: Q1.2, Q2.2
unnamed: Q1.3, Q2.3
unnamed: Q3.1, R4.2
unnamed: J13.1, Q2.5, R5.2
unnamed: J13.2, Q2.6, R5.1
unnamed: J13.6, Q2.7, R6.2
unnamed: J13.3, Q2.8, R6.1
PANIC: J12.2, Q1.27, R12.1
QBATTERY1: Q8.1, Q10.7
QBATTERY2: Q7.1, Q11.7
S1_HIGH: C15.1, P2.4, Q10.8
S2_HIGH: C16.1, P3.4, Q11.8
S_BATTERY: Q1.15, Q10.2, Q11.2
S_BUCK: Q1.16, Q6.2
TEMP: Q1.28, Q4.17
TEMP1: J2.4, Q4.23
TEMP2: J3.4, Q4.22
TEMP3: J4.4, Q4.21
TEMP4: J5.4, Q4.20
TEMP5: J6.4, Q4.19
TEMP6: J7.4, Q4.18
TEMP7: J8.4, Q4.16
TEMP8: Q4.15, Q5.2
VB: C13.1, P1.4, Q6.8
VIN: C27.1, Q4.2, R20.1, R21.2
VOLTS: Q1.26, Q4.1
VOLTS1: J2.5, Q4.9
VOLTS2: J3.5, Q4.8
VOLTS3: J4.5, Q4.7
VOLTS4: J5.5, Q4.6
VOLTS5: J6.5, Q4.5
VOLTS6: J7.5, Q4.4
VOLTS7: J8.5, Q4.3
VS: C13.2, D1.2, D1.4, P1.3, Q3.3, Q6.6, Q9.3, Q9.4
V_MAIN: C12.1, Q1.23, R2.1, R3.2

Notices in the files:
parts and their libraries:
SparkFun-DigitalIC: Licensing: CC v3.0 Share-Alike You are welcome to use this library for commercial purposes.
LilyPad-Wearables: Licensing:Creative Commons ShareAlike 4.0 International - https://creativecommons.org/licenses/by-sa/4.0
